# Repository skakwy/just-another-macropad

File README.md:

KEEB Mechanical Macropad

Overview

KEEB Macropad is a compact mechanical macropad designed to enhance your productivity and workflow. With its sleek design and customizable features, this macropad is perfect for gamers, programmers, and anyone who wants to streamline their tasks.

Features

13 mechanical keys with and two rotary encoders
Customizable firmware for macros and keymaps
Compact and portable design for easy portability
Renders

Check out the renders of the macropad in the render: render directory. These renders give you a visual preview of the macropad's design and features.

BOM (Bill of Materials)

The bill of materials (BOM) lists all the components required to build the macropad. You can find the BOM in the BOM.md: (comming soon)

Build Instructions

Detailed build instructions will be provided in a future release.

Firmware

The firmware for the macropad is constantly under development. To stay up-to-date with the latest firmware, please follow the project on GitHub.

Contributing

We welcome contributions to this project! If you have any ideas for new features or improvements, please feel free to open a pull request.

License

This project is licensed under the MIT License. For more information, please refer to the LICENSE: LICENSE file.

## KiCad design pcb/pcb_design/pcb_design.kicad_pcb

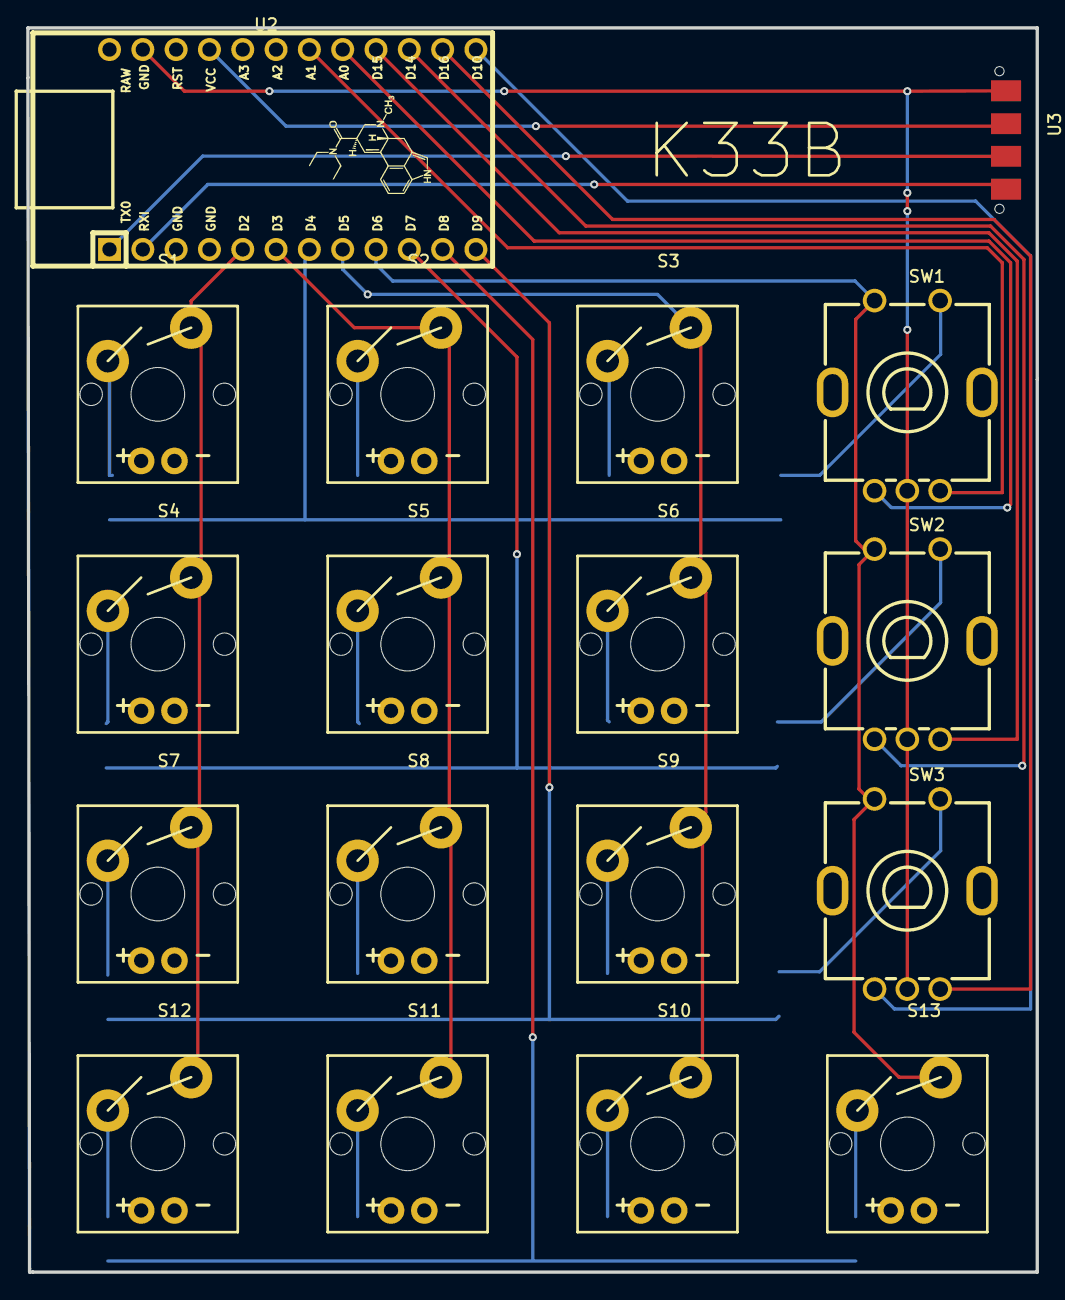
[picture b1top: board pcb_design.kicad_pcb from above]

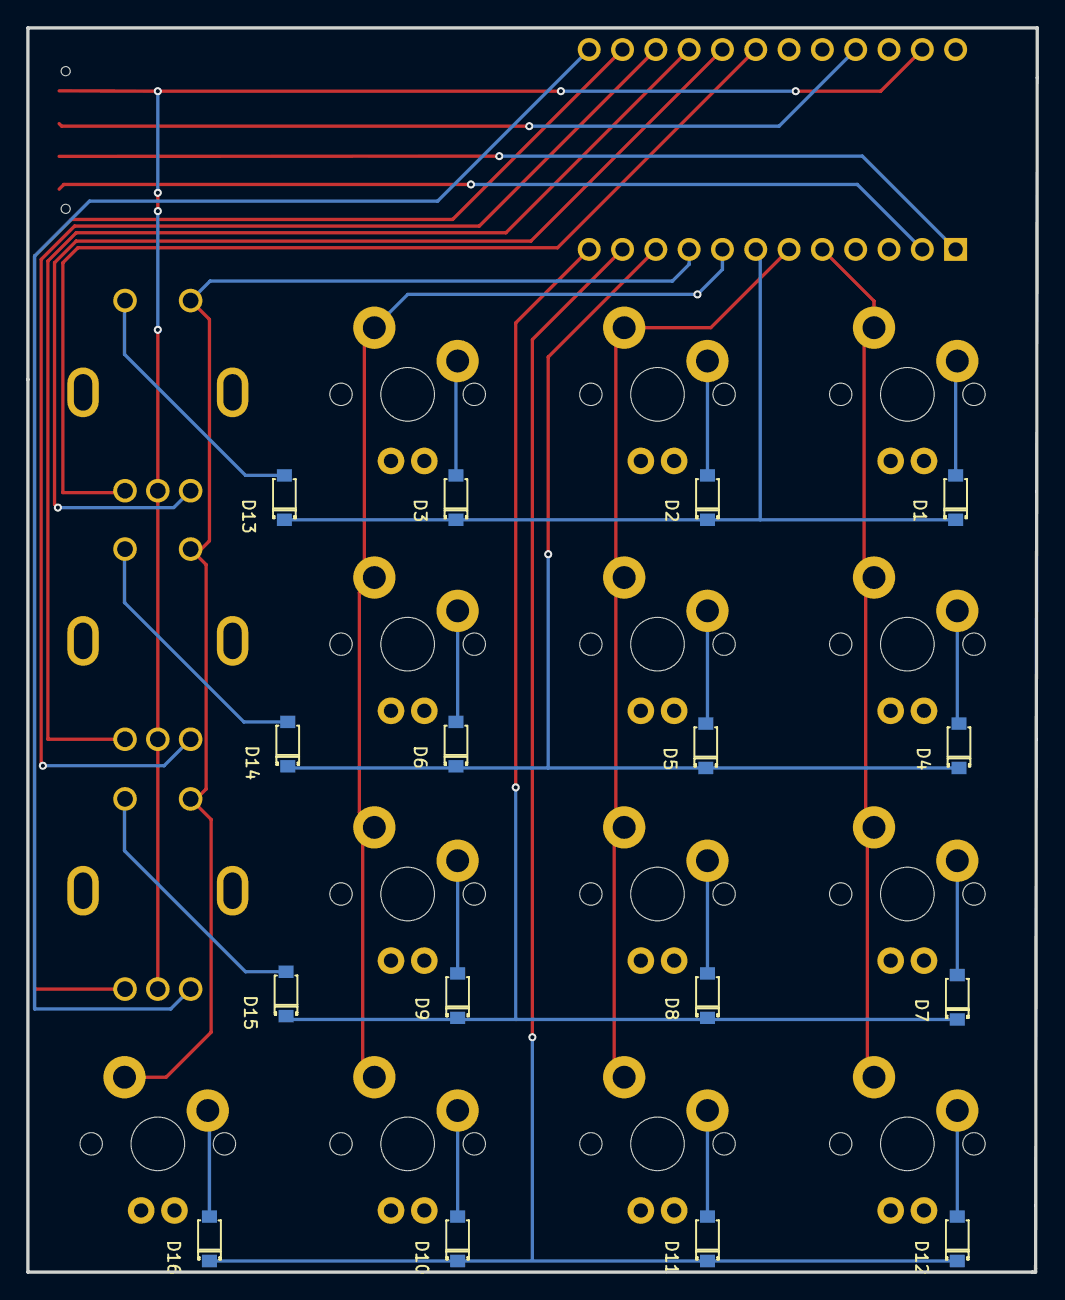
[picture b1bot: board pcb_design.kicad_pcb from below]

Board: 2 copper layers, 77.0 x 94.9 mm, 34 parts (16 on the bottom side), 34 nets.

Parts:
D1, D2, D3, D4, D5, D6, D7, D8, D9, D10, D11, D12, D13, D14, D15, D16: 1N4007W; SOD-123_L2.8-W1.8-LS3.7-RD
S1, S2, S3, S4, S5, S6, S7, S8, S9, S10, S11, S12, S13: CHERRY_CHERRY_MX; CHERRY-MX-LED-1U
SW1, SW2, SW3: PEC11R-4015F-S0024; SW-TH_PEC11R-4XXXF-SXXXX
U2: PROMICRO TYPE C 32U4-AU TH COPY; PROMICRO TYPE C 32U4-AU TH
U3: pogo 4 pin connector; POGO 4 PIN

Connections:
A1: SW1.A, U2.17
A2: SW2.A, U2.15
A3: SW3.A, U2.13
B1: SW1.B, U2.18
B2: SW2.B, U2.16
B3: SW3.B, U2.14
COL0: S1.S2, S4.S2, S7.S2, S12.S2, U2.5
COL1: S2.S2, S5.S2, S8.S2, S11.S2, U2.6
COL2: S3.S2, S6.S2, S9.S2, S10.S2, U2.8
COL3: S13.S2, SW1.1, SW2.1, SW3.1, U2.9
D2_2: D2.2, S2.S1
D3_2: D3.2, S3.S1
D10_2: D10.2, S10.S1
D11_2: D11.2, S11.S1
D12_2: D12.2, S12.S1
GND: SW1.C, SW2.C, SW3.C, U2.3, U2.4, U2.23, U3.1
ROW0: D1.1, D2.1, D3.1, D13.1, U2.7
ROW1: D4.1, D5.1, D6.1, D14.1, U2.10
ROW2: D7.1, D8.1, D9.1, D15.1, U2.12
ROW3: D10.1, D11.1, D12.1, D16.1, U2.11
RX: U2.2, U3.4
S1_S1: D1.2, S1.S1
S4_S1: D4.2, S4.S1
S5_S1: D5.2, S5.S1
S6_S1: D6.2, S6.S1
S7_S1: D7.2, S7.S1
S8_S1: D8.2, S8.S1
S9_S1: D9.2, S9.S1
S13_S1: D16.2, S13.S1
SW1_2: D13.2, SW1.2
SW2_2: D14.2, SW2.2
SW3_2: D15.2, SW3.2
TX: U2.1, U3.3
VCC: U2.21, U3.2

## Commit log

2024-01-18 first render
2024-01-18 Create LICENSE
2024-01-18 gitignore
